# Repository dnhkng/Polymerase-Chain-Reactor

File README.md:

Polymerase-Chain-Reactor
========================

An Open Source PCR machine for DIY Recombinant Genetics, and entry to the Hackaday Prize! If you like it, please Skull it at http://hackaday.io/project/1864-%245-Polymerase-Chain-Reactor

This project describes the designs for a remarkably simple but fully functional DNA replicator, based around the Arduino platform, and utilizing just a handful of components. The trick is to use multiple physical process driven by just heat! Heat drives DNA conversion between its single and double strand state; alters the activity of the polymerase to copy DNA; and drives circulation of the reaction medium via convection. So, it's all and heat and geometry, intead of trying to shift temperature as fast and accurately as possible with expensive hardware. 

It uses the Arduino libraries, and the Arduino PID Library by Brett Beauregard.

Eagle schematics and a boards layout files are also included.

The project is GPLv3 licenced

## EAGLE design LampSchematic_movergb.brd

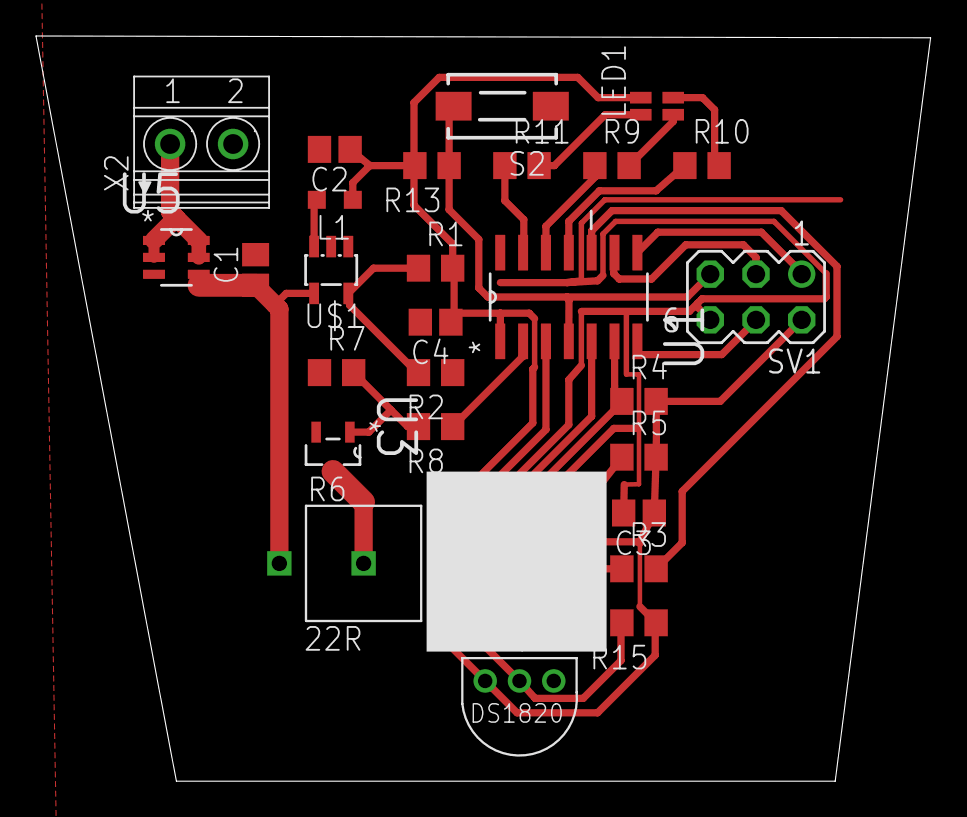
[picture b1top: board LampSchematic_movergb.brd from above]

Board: 2 copper layers, 49.7 x 41.4 mm, 29 parts (0 on the bottom side), 24 nets.

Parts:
C1, C3, C4: 0.1uF; C0805
C2: 10uF; C0805
L1: 10uH; L2012C
LED1: GM1WA55311A
R1: 61.9k; R0805
R2: 20k; R0805
R3, R15: 6.8R; R0805
R4, R5: 4.7k; R0805
R6: 22R; 5WRESISTOR
R7: 100k; R0805
R8: 47R; R0805
R9: 330R; R0805
R10, R11: 68R; R0805
R13: 10k; R0805
S2: DTSM-3
SV1: ISP; MA03-2
U1: ATTINY84-20SSU; SOIC127P600X175-14N
U2: VEML6040
U3: PMV20ENR; SOT95P230X110-3N
U5: Si3417DV; SOP95P285X110-6N
U$1: TPS560200; SOT23-5L
U$2: DS1820TO92; DS1820
U$3: UV; GM5BW96385A
X2: 1751248

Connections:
+12V: C1.1, R6.P$2, U5.4, U$1.4
BLUE: R11.1, U1.13
GND: C1.2, C2.2, C3.2, C4.2, R2.1, R7.1, S2.1, SV1.6, U1.14, U2.1, U3.2, U5.3, U$1.2, U$2.GND, U$3.2, X2.2
GREEN: R10.1, U1.11
HEAT: R8.1, U1.2
MISO: SV1.1, U1.8
MOSI: SV1.4, U1.7
unnamed: L1.2, U$1.3
unnamed: R1.1, R2.2, U$1.5
unnamed: R6.P$1, U3.3
unnamed: R7.2, R8.2, U3.1
unnamed: LED1.2, R9.2
unnamed: LED1.3, R10.2
unnamed: LED1.1, R11.2
unnamed: R3.1, U$3.1
unnamed: U5.1, U5.2, U5.5, U5.6, X2.1
RED: R9.1, U1.12
RES: R13.1, S2.2, SV1.5, U1.4
SCK: SV1.3, U1.9
SCLK: R5.1, U1.5, U2.3
SDAT: R4.1, U1.6, U2.2
TEMP: R15.2, U1.3, U$2.DQ
UV: R3.2, U1.10
VCC: C2.1, C3.1, C4.1, L1.1, LED1.4, R1.2, R4.2, R5.2, R13.2, R15.1, SV1.2, U1.1, U2.4, U$2.VDD

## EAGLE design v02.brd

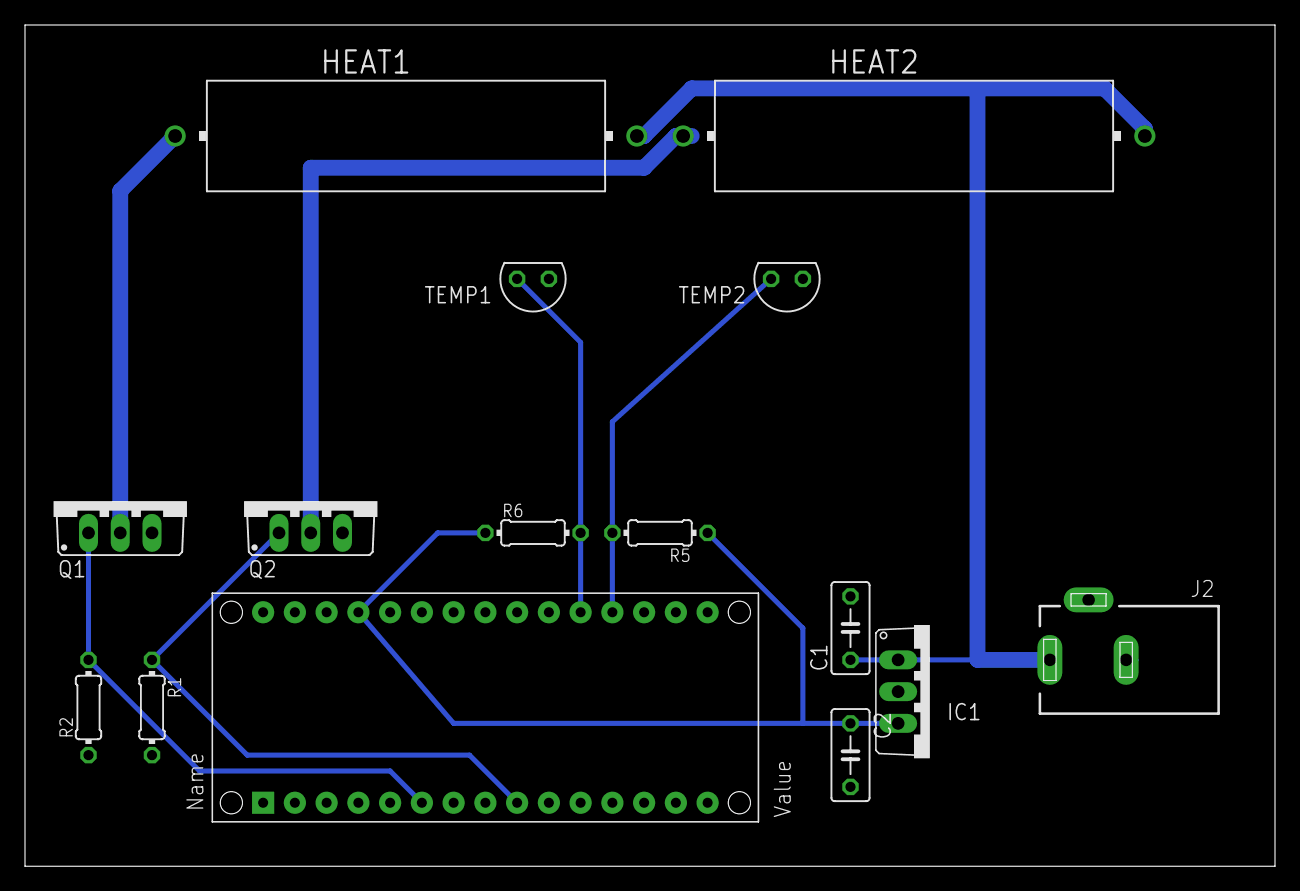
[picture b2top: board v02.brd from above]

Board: 2 copper layers, 100.0 x 67.3 mm, 15 parts (0 on the bottom side), 9 nets.

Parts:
C1, C2: C050-030X075
HEAT1, HEAT2: 10; HPS932
IC1: 7805TV; TO220V
J2: DCJ0303
Q1, Q2: IRF740; TO220BV
R1, R2: 10K; 0204/7
R5, R6: 2K; 0204/7
TEMP1, TEMP2: LM335; TO92H
U$1: PDIP-32

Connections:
+5V: C2.1, IC1.3, R5.1, R6.1, U$1.+5V
GND: C1.2, C2.2, IC1.2, J2.2, J2.3, Q1.S, Q2.S, R1.2, R2.1, TEMP1.1, TEMP2.1, U$1.GND, U$1.GND1
H1: Q1.G, R2.2, U$1.D3
H2: Q2.G, R1.1, U$1.D6
unnamed: HEAT1.1, Q1.D
unnamed: HEAT2.1, Q2.D
T1: R6.2, TEMP1.2, U$1.A6
T2: R5.2, TEMP2.2, U$1.A7
V+: C1.1, HEAT1.2, HEAT2.2, IC1.1, J2.1

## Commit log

2014-08-12 First Upload
    Arduino 1.0.5 code for the Polymerase Chain Reactor, and entry in the
    Hackaday Prize
2014-08-13 Schematics and PCB designs
    A simple single-sided board for the Arduino Nano based device.
2014-08-19 System Design Documents
2014-09-26 The second, more sophisticated PCR machine
    Arduino code - Initial upload
2014-09-26 Renamed project
2014-09-26 Renaming
2014-09-26 Bugfix
2014-09-26 Lots of changes
2014-09-27 Name changes
2014-09-30 Code tidy-up
2015-08-31 LAMP project
    first commit of schematic and board
2015-09-01 updates the LAMP stuff
    Better layout for the PCB
